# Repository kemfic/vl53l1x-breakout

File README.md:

vl53l1x-breakout
---
NOTE: needs a PCA9615 on master side to convert differential i2c back to i2c. will post another breakout for this soon.

license
---
MIT License

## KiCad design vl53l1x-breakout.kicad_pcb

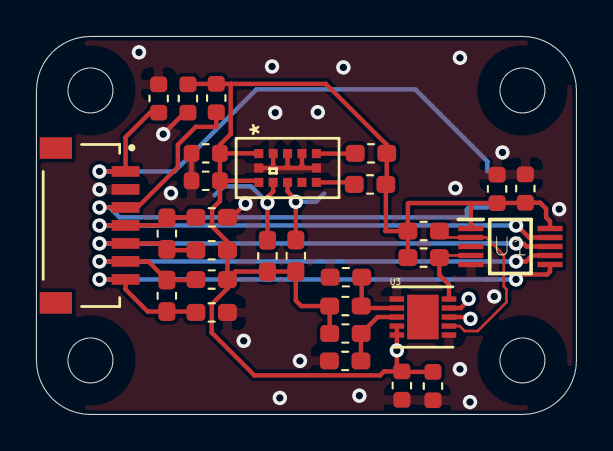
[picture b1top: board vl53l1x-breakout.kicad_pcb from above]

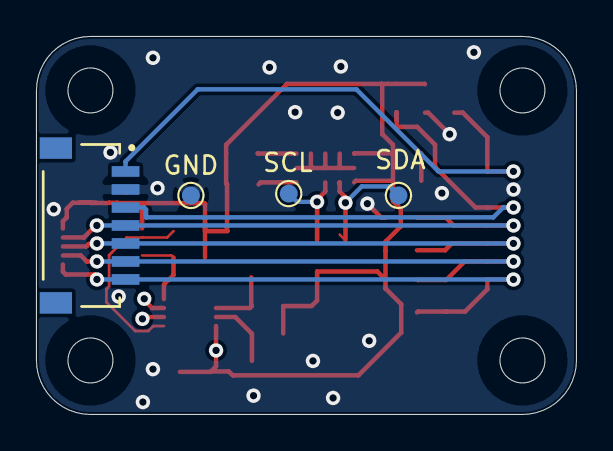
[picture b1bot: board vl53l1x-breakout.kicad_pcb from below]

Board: 4 copper layers, 30.0 x 21.0 mm, 33 parts (4 on the bottom side), 16 nets.

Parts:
C1, C4: 10uF; C_0603_1608Metric
C2, C3, C5: 0.1uF; C_0603_1608Metric
C6, C8: 4.7uF; C_0603_1608Metric
C7: 0.01uF; C_0603_1608Metric
FB1: Ferrite_Bead_Small; L_0603_1608Metric
GND: TestPoint_Pad_D1.0mm
J0, J1: SM07B-SRSS-TBLFSN; JST-SM07B-SRSS-TBLFSN-0
R1, R3, R4, R6: 390; R_0603_1608Metric_Pad1.05x0.95mm_HandSolder
R2, R5: 120; R_0603_1608Metric_Pad1.05x0.95mm_HandSolder
R7, R8, R15, R16: 4.7k; R_0603_1608Metric_Pad1.05x0.95mm_HandSolder
R9: DNP; R_0603_1608Metric_Pad1.05x0.95mm_HandSolder
R10: 0; R_0603_1608Metric_Pad1.05x0.95mm_HandSolder
R11, R14: 10k; R_0603_1608Metric_Pad1.05x0.95mm_HandSolder
R12: 976; R_0603_1608Metric_Pad1.05x0.95mm_HandSolder
R13: 102; R_0603_1608Metric_Pad1.05x0.95mm_HandSolder
SCL: TestPoint_Pad_D1.0mm
SDA: TestPoint_Pad_D1.0mm
U1: PCA9615DPJ; PCA9615_SOP50P490
U2: VL53L1CXV0FY_1; VL53L1CXV0FY
U3: LTC4316IDD#PBF; DFN-10_DD

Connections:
+3V3: FB1.1, J0.3, J1.3
GND: C1.2, C2.1, C3.2, C4.2, C5.2, C6.2, C7.2, C8.2, GND.1, J0.2, J1.2, R3.2, R6.2, R10.2, R13.2, U1.5, U2.2, U2.3, U2.4, U2.6, U2.12, U3.1, U3.6
unnamed: R9.2, R10.1, U3.3
unnamed: R11.1, U2.5
unnamed: R12.2, R13.1, U3.2
unnamed: R14.2, U2.7
unnamed: R15.2, SCL.1, U2.9, U3.8
unnamed: R16.2, SDA.1, U2.10, U3.9
SCL: R7.2, U1.4, U3.10
SCL+: J0.6, J1.6, R4.2, R5.1, U1.7
SCL-: J0.7, J1.7, R5.2, R6.1, U1.6
SDA: R8.2, U1.2, U3.7
SDA+: J0.5, J1.5, R1.2, R2.1, U1.8
SDA-: J0.4, J1.4, R2.2, R3.1, U1.9
VCC: C2.2, C3.1, C4.1, C5.1, C6.1, C7.1, C8.1, FB1.2, R1.1, R4.1, R7.1, R8.1, R9.1, R11.2, R12.1, R14.1, R15.1, R16.1, U1.1, U1.10, U2.1, U2.11, U3.4, U3.5
shld: C1.1, J0.1, J1.1

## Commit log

2021-02-28 [readme] update
2021-02-28 [PCA9615] DSCL termination and biasing
2021-02-28 [schematic] done, components numbers left blank for now
2021-03-01 [schematic] added connectors
2021-03-01 [schematic] update pdf
2021-03-01 [board] begin layout
2021-03-07 [layout] smaller components; have some idea of board size
2021-03-08 [LTC4316] update footprint
2022-01-14 [layout] complete overhaul
2022-01-14 fixed connector pinouts
2022-01-14 slightly cleaner
2022-01-14 cleanup routing a bit
2022-01-15 ordered but the pinout is flipped :/
2022-01-16 [rev.1] fixed connector pinout
2022-01-30 push
2022-04-04 using 0603s now

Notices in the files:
parts and their libraries:
Copyright 2016 Accelerated Designs. All rights reserved.
